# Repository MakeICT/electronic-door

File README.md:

# Master Control Program 

This system is used to secure spaces with an electronic door latch.

## Dependencies:
* [Node + NPM](Node.js)
* [PostgreSQL](http://www.postgresql.org/)
* [Arduino 1.6.5](https://www.arduino.cc/)

## Hardware requirements: 
* [Server protocol RS-485](https://en.wikipedia.org/wiki/RS-485) for the server/client communication.
* [Arduino Nano](https://www.arduino.cc/) for the door client (This is required for the matching footprint).
* [NFC reader](https://www.adafruit.com/products/364). This is the one that we are using for our version of the door lock. 

* * *

## Todo
* Server
	* Super admins vs group admins
	* Make plugins respect disabled mode
	* When unlocking from web ui, display user in log
	
* Client
	* New NFC reader
	* Add doorbell input (capacitive?)
	* Design/build case for front
	* Build 2nd client for testing & back door

## License 

> Copyright (C) 2014-2016 MakeICT
> 
> This program is free software: you can redistribute it and/or modify it 
> under the terms of the GNU General Public License as published by the 
> Free Software Foundation, either version 3 of the License, or (at your 
> option) any later version.
> 
> This program is distributed in the hope that it will be useful, but 
> WITHOUT ANY WARRANTY; without even the implied warranty of 
> MERCHANTABILITY or FITNESS FOR A PARTICULAR PURPOSE.  See the GNU 
> General Public License for more details.
> 
> You should have received a copy of the GNU General Public License along 
> with this program.  If not, see [The GNU licenses page](http://www.gnu.org/licenses)
    
* * *

This is a work in progress. For more information, please visit the [MakeICT Wiki](http://makeict.org/wiki/index.php/Electronic_Door_Entry).

* * *

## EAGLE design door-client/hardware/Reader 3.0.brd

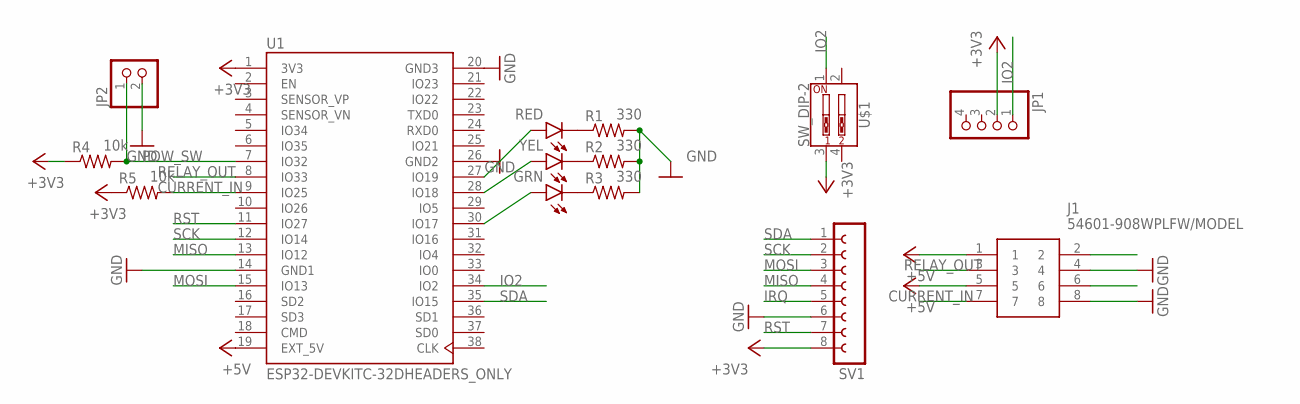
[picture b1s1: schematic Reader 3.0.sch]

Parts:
GRN: LED5MM
J1: 54601-908WPLFW/MODEL; HDRV4W64P254_1X4_1016X508X838B
JP1: PINHD-1X4/90; 1X04/90
JP2: PINHD-1X2/90; 1X02/90
R1, R2, R3: 330; 0204/7
R4, R5: 10k; 0204/7
RED: LED5MM
SV1: FE08-1; HDR_F_1X8
U1: ESP32-DEVKITC-32DHEADERS_ONLY; ESP32_DEVKITC_DIP
U$1: SW_DIP-2
YEL: LED5MM

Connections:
+3V3: JP1.2, R4.1, R5.1, SV1.8, U1.1 (3V3), U$1.3
+5V: J1.1, J1.5, U1.19 (EXT_5V)
CURRENT_IN: J1.7, R5.2, U1.9 (IO25)
GND: J1.4, J1.8, JP2.2, R1.2, R2.2, R3.2, SV1.6, U1.14 (GND1), U1.20 (GND3), U1.26 (GND2)
IO2: JP1.1, U1.34 (IO2), U$1.1
IRQ: SV1.5
MISO: SV1.4, U1.13 (IO12)
MOSI: SV1.3, U1.15 (IO13)
unnamed: GRN.A, U1.30 (IO17)
unnamed: U1.28 (IO18), YEL.A
unnamed: RED.A, U1.27 (IO19)
unnamed: R1.1, RED.K (C)
unnamed: R2.1, YEL.K (C)
unnamed: GRN.K (C), R3.1
POW_SW: JP2.1, R4.2, U1.7 (IO32)
RELAY_OUT: J1.3, U1.8 (IO33)
RST: SV1.7, U1.11 (IO27)
SCK: SV1.2, U1.12 (IO14)
SDA: SV1.1, U1.35 (IO15)

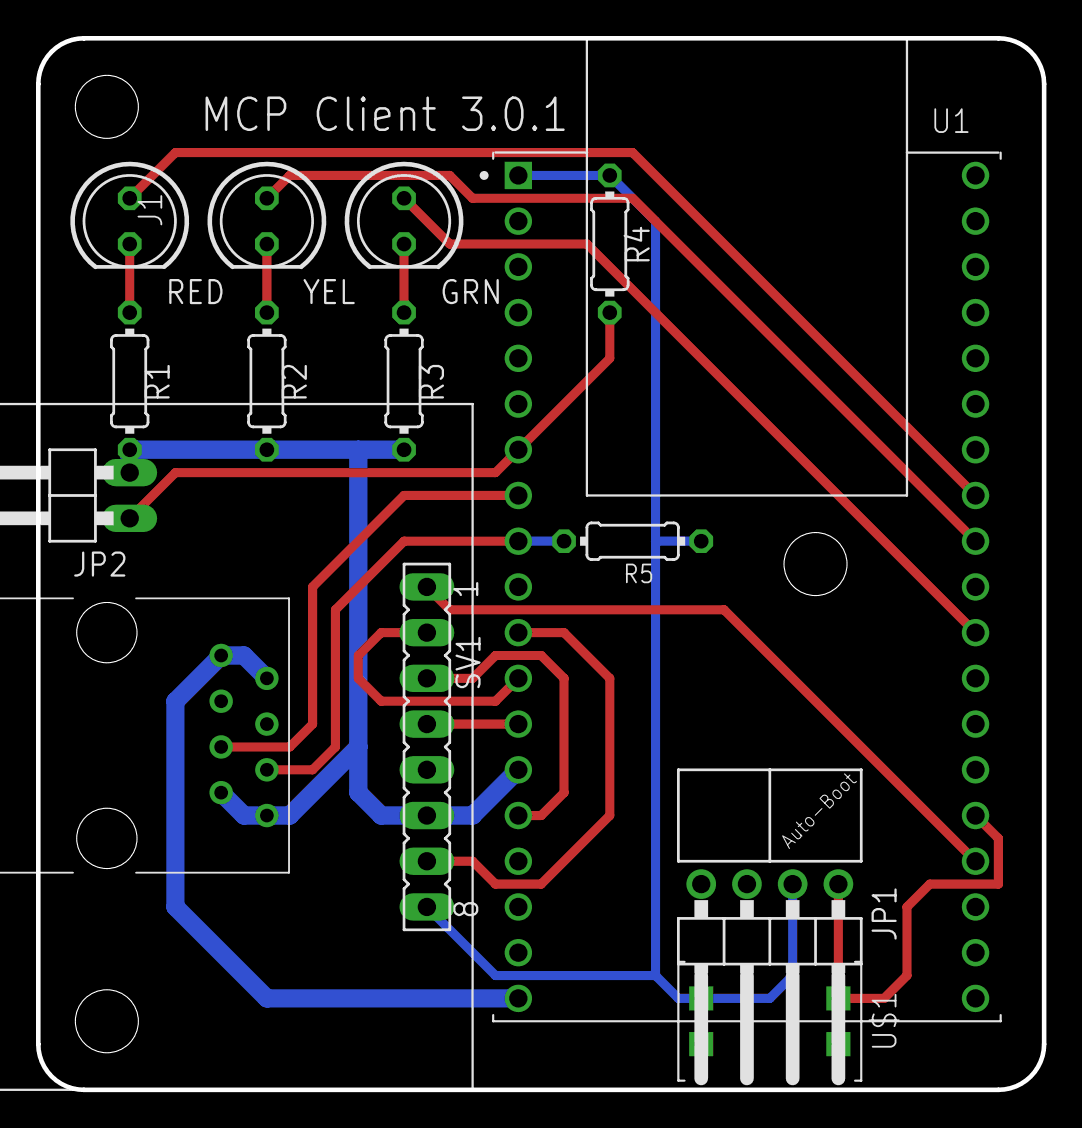
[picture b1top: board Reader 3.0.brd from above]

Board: 2 copper layers, 55.9 x 58.4 mm, 14 parts (0 on the bottom side), 18 nets.

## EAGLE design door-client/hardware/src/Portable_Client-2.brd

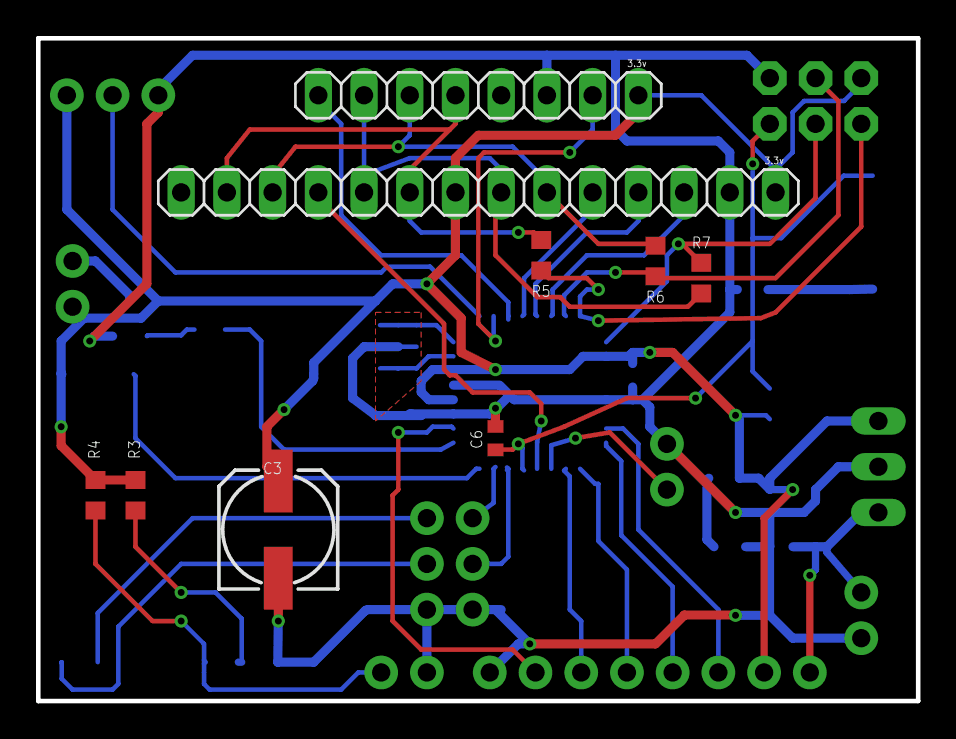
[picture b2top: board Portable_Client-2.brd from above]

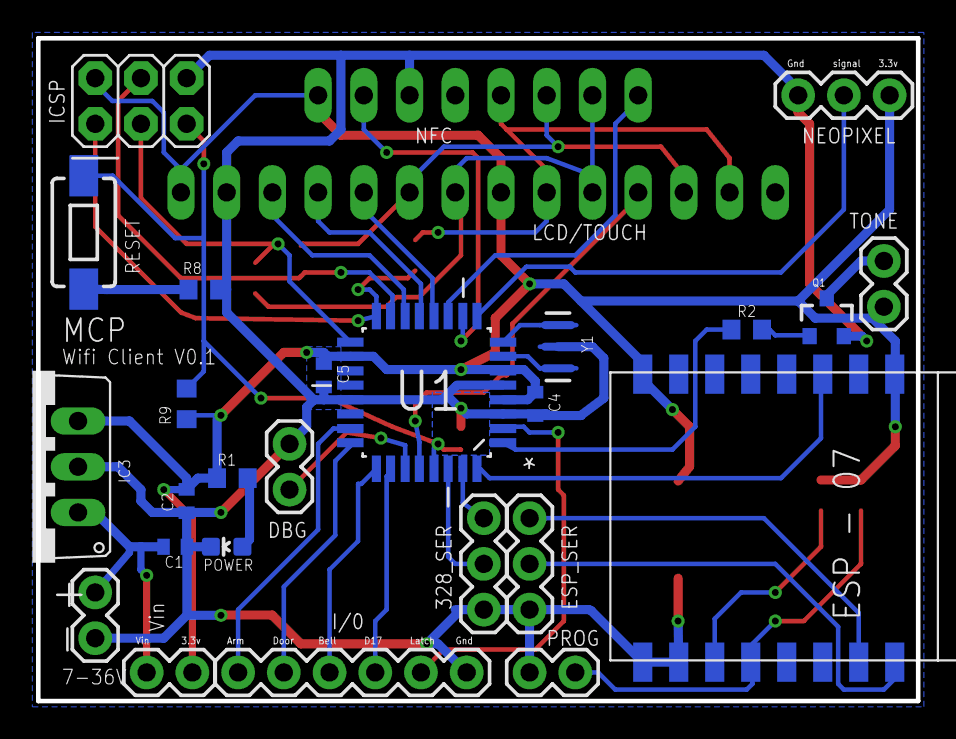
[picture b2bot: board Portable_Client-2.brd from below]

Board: 2 copper layers, 48.9 x 36.8 mm, 34 parts (25 on the bottom side), 37 nets.

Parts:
328_SER: 1X03
C1, C2: C0402
C3: 100uf; 153CLV-0605
C4, C5, C6: .1uf; C0402
DBG, DBG1: 1X02
ESP_SER: 1X03
I/0: 1X06
IC3: MC78M05ABT; TO220V
ICSP: 2X03
LCD/TOUCH: 1X14
NEOPIXEL: 1X03
NFC: 1X08
POW: 1X02
POWER: LED-0603
PROG: 1X02
Q1: SOT23-3
R1, R2, R5, R6, R7, R8: 330; R0603
R3, R4: 3.3k; R0603
R9: 4.7k; R0603
RESET: SWITCH-MOMENTARY-2SMD-1101NE; TACTILE-SWITCH-1101NE
TONE: 1X02
U1: ATMEGA328P-AU; QFP80P900X900X120-32N
U$2: ESP07-AITHINKER
Y1: 12MHZ; RESONATOR-SMD

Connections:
0SC2: U1.8, Y1.3
3V3: C2.1, C3.+, C4.1, C5.1, DBG1.2, IC3.3, ICSP.2, LCD/TOUCH.7, LCD/TOUCH.14, NEOPIXEL.1, NFC.1, R1.2, R3.1, R4.1, R9.1, TONE.1, U1.4, U1.6, U1.18, U$2.RESET1, U$2.VCC1
D0: 328_SER.2, U1.30
D1: 328_SER.3, U1.31
D2: U1.32, U$2.CH_PD1
D3: R2.2, U1.1
D4: I/0.2, U1.2
D5: NEOPIXEL.2, U1.9
D6: NFC.2, U1.10
D7: NFC.8, U1.11
D8: LCD/TOUCH.10, U1.12
D9: LCD/TOUCH.11, U1.13
D10: LCD/TOUCH.12, U1.14
D11: ICSP.4, R6.1, U1.15
D12: ICSP.1, R5.1, U1.16
D13: ICSP.3, R7.1, U1.17
D14: I/0.6, U1.23
D15: I/0.5, U1.24
D16: I/0.4, U1.25
D17: I/0.3, U1.26
D18: DBG.1, U1.27
D19: LCD/TOUCH.4, U1.28
ESP_RX: ESP_SER.3, U$2.RX1
ESP_TX: ESP_SER.2, U$2.TX1
GND: 328_SER.1, C1.2, C2.2, C3.-, C4.2, C5.2, C6.2, DBG.2, ESP_SER.1, I/0.1, IC3.2, ICSP.6, LCD/TOUCH.13, NEOPIXEL.3, NFC.3, POW.1, POWER.C, PROG.1, Q1.2, R8.1, U1.3, U1.5, U1.21, U$2.GND1, U$2.GPIO15, Y1.2
MISO: LCD/TOUCH.2, LCD/TOUCH.6, NFC.5, R5.2
MOSI: LCD/TOUCH.3, LCD/TOUCH.9, NFC.6, R6.2
unnamed: Q1.3, TONE.2
unnamed: Q1.1, R2.1
unnamed: R8.2, RESET.2
unnamed: PROG.2, R4.2, U$2.GPIO0
unnamed: R3.2, U$2.GPIO2
unnamed: POWER.A, R1.1
OSC1: U1.7, Y1.1
RESET: C6.1, ICSP.5, R9.2, RESET.1, U1.29
SCK: LCD/TOUCH.5, LCD/TOUCH.8, NFC.7, R7.2
VIN: C1.1, DBG1.1, IC3.1, POW.2

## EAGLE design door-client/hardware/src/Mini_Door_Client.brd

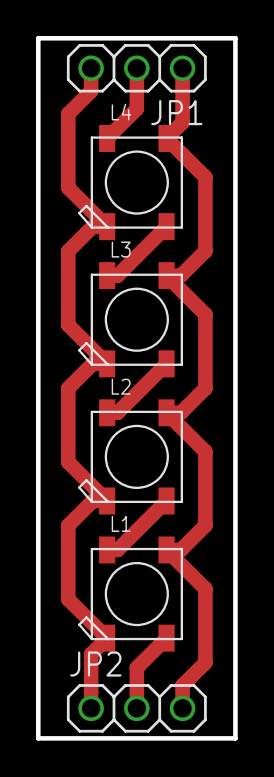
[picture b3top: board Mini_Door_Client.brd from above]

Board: 2 copper layers, 11.0 x 38.9 mm, 6 parts (0 on the bottom side), 7 nets.

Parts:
JP1, JP2: 1X03
L1, L2, L3, L4: WS2812B

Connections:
+5V: JP1.1, JP2.3, L1.1-VDD, L2.1-VDD, L3.1-VDD, L4.1-VDD
GND: JP1.3, JP2.1, L1.3-GND, L2.3-GND, L3.3-GND, L4.3-GND
unnamed: L1.2-DOUT, L2.4-DIN
unnamed: L2.2-DOUT, L3.4-DIN
unnamed: L3.2-DOUT, L4.4-DIN
unnamed: JP1.2, L4.2-DOUT
unnamed: JP2.2, L1.4-DIN

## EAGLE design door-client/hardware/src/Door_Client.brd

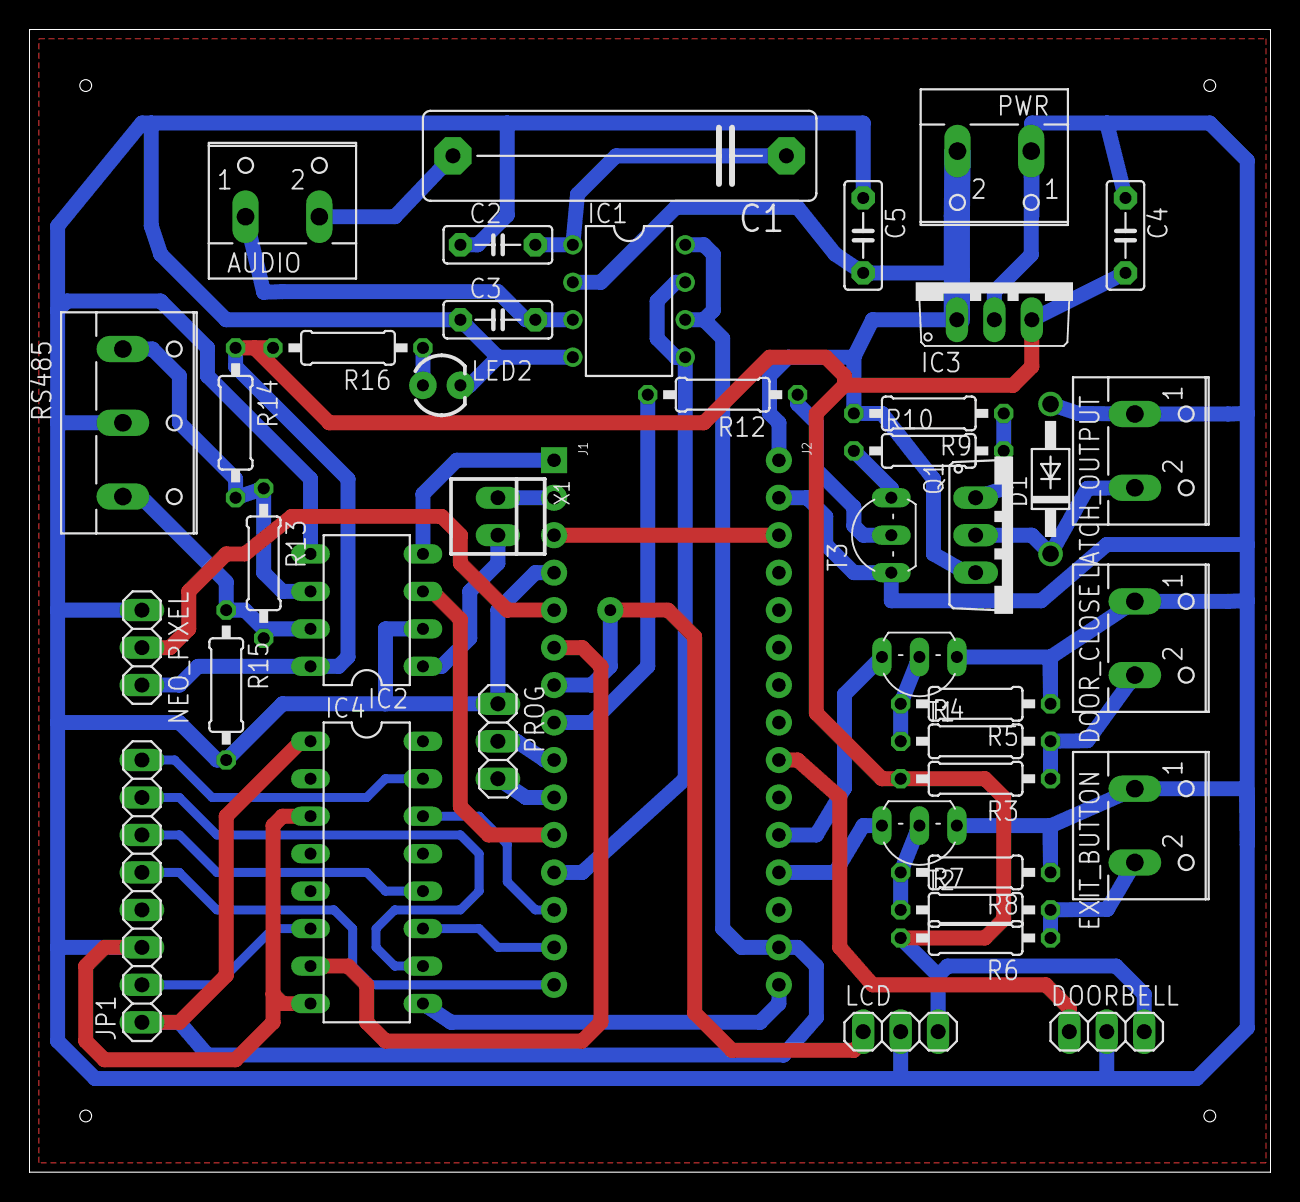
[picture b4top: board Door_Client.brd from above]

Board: 2 copper layers, 84.1 x 77.5 mm, 42 parts (0 on the bottom side), 41 nets.

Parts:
AUDIO: W237-102
C1: 10uf; C22.5B6
C2, C3, C4, C5: .1uf; C5B2.5
D1: 1N4004; DO41-10
DOORBELL: 1X03
DOOR_CLOSE: W237-102
EXIT_BUTTON: W237-102
IC1: L272M; DIL08
IC2: MAX3468EPA; DIL08
IC3: MC78M05ABT; TO220V
IC4: 4050N; DIL16
J1: HEAD15-NOSS
J2: HEAD15-NOSS-1
JP1: 1X08
LATCH_OUTPUT: W237-102
LCD: 1X03
LED2: LED3MM
NEO_PIXEL: 1X03
PROG: 1X03
PWR: W237-102
Q1: TIP42C; TO220AV
R3, R4, R5, R6, R7, R8, R9: 10K; 0207/10
R10: 2k; 0207/10
R12: 0207/10
R13: 100; 0207/10
R14, R15: 20K; 0207/10
R16: 330; 0207/10
RS485: W237-103
T1, T2, T3: TO92-EBC
X1: 22-23-2021

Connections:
3V3: IC1.6, IC1.8, IC4.1, J2.14, JP1.1
+5V: C4.2, DOORBELL.3, IC2.8, IC3.3, LCD.3, NEO_PIXEL.3, R3.2, R6.2, R14.1, R16.2
A0: J2.12, T2.C
A1: J2.11, T1.C
A3: DOORBELL.1, J2.9
COM: C2.1, C3.1, C4.1, C5.1, D1.A, DOORBELL.2, DOOR_CLOSE.1, EXIT_BUTTON.1, IC1.4, IC2.2, IC2.5, IC3.2, IC4.3, IC4.8, J1.4, J2.2, JP1.3, LATCH_OUTPUT.1, LCD.2, LED2.K, NEO_PIXEL.1, PROG.1, PWR.1, R5.1, R8.1, R15.2, RS485.2, T1.E, T2.E, T3.E
D2: J1.5, NEO_PIXEL.2
D3: IC4.7, J1.6
D4: J1.7, LCD.1
D6: J1.2, X1.1
D7: IC2.4, J1.1
D8: IC2.3, J1.11
D9: IC1.5, IC1.7, J1.12
D10: IC4.14, J1.13
D11/MOSI: IC4.11, J1.14
D12/MISO: J1.15, JP1.5
D13: J1.8, R12.2
unnamed: D1.C, LATCH_OUTPUT.2, Q1.C
unnamed: R12.1, T3.B
unnamed: IC4.6, JP1.2
unnamed: IC2.7, R13.2, R15.1, RS485.3
unnamed: IC2.6, R13.1, R14.2, RS485.1
unnamed: J1.9, PROG.2
unnamed: C1.1, C2.2, IC1.1
unnamed: AUDIO.2, C1.2
unnamed: AUDIO.1, C3.2, IC1.3
unnamed: LED2.A, R16.1
unnamed: R4.1, R5.2, T1.B
unnamed: DOOR_CLOSE.2, R3.1, R4.2
unnamed: R7.1, R8.2, T2.B
unnamed: EXIT_BUTTON.2, R6.1, R7.2
unnamed: R10.1, T3.C
unnamed: Q1.B, R9.1, R10.2
unnamed: IC4.10, JP1.7
unnamed: IC4.12, JP1.6
unnamed: IC4.15, JP1.8
unnamed: J1.10, PROG.3
unnamed: IC4.9, J2.15
unnamed: IC2.1, X1.2
RESET: J1.3, J2.3
VIN: C5.2, IC1.2, IC3.1, J2.1, PWR.2, Q1.E, R9.2

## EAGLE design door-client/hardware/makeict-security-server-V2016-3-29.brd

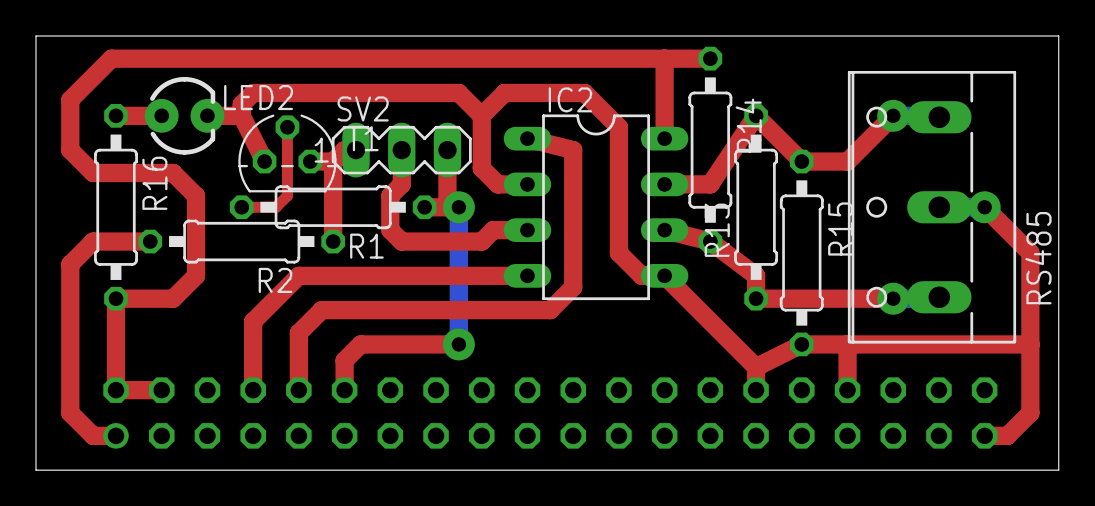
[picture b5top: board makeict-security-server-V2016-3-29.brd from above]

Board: 2 copper layers, 56.8 x 24.1 mm, 12 parts (1 on the bottom side), 12 nets.

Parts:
IC2: MAX3468EPA; DIL08
LED2: LED3MM
R1, R2: 4.7K; 0207/10
R13: 100; 0207/10
R14, R15: 20K; 0207/10
R16: 330; 0207/10
RS485: W237-103
SV1: FE20-2
SV2: MA03-1
T1: 2N3904; TO92

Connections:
+3V3: R2.2, SV1.1, SV1.17
+5V: IC2.8, R14.1, R16.2, SV1.2, SV1.4
COM: IC2.2, IC2.5, LED2.K, R15.2, RS485.2, SV1.6, SV1.9, SV1.14, SV1.20, SV1.25, SV1.30, SV1.34, SV1.39, T1.3
D7: IC2.4, SV1.8
D8: IC2.3, SV2.2
unnamed: R1.1, SV1.12, SV2.3
unnamed: R1.2, T1.2
unnamed: R2.1, SV2.1, T1.1
unnamed: IC2.7, R13.2, R15.1, RS485.3
unnamed: IC2.6, R13.1, R14.2, RS485.1
unnamed: LED2.A, R16.1
unnamed: IC2.1, SV1.10

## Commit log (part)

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2016-04-04 show login if authentication is stale
2016-04-04 rename to system tools; add system tools
2016-04-04 fix bug from bad copy-paste
2016-04-06 force door unlock duration to 2 bytes
2016-04-06 fix for 2 byte duration
2016-04-06 add more logging
2016-04-06 wrong code
2016-04-06 drop masonry
2016-04-06 fix plugin action button appearance
2016-04-06 fix error on unauth
2016-04-06 forgot serial patches
2016-04-06 don't strip spaces
2016-04-06 center plugin enable/disable buttons
2016-04-06 fix wildapricot group bug; better logging
2016-04-06 front-end UX improvements
2016-04-06 fix bug with enable/disable plugin
2016-04-06 fix bug when enable/disable plugins
2016-04-13 add delay before issuing system commands
2016-04-19 change user display to wells
2016-04-19 autoload user groups
2016-04-20 add basic chime stuff
2016-04-20 allow users to add groups
2016-04-20 add tone for alarm
2016-04-27 change plugin option format
2016-04-27 holy crap, you can BIND functions to a THIS arg before calling them?! Sweet jesus.
2016-04-27 fix packet queing system maybe...
2016-04-27 eliminate race condition with plugin settings load. Asynch is not my friend :(
2016-04-28 fix plugin loading bug on first run
2016-05-01 fix serial boo-boos - don't wait for response on ACKs and resend the last non-ACK packet. Oops. - properly increment transaction ID when sending new packets
2016-05-04 only send to clients who have this plugin installed
2016-05-04 fix installation bug with client plugins
2016-05-04 add ability to update clients
2016-05-04 super serial needs to know when a client plugin id is updated
2016-05-04 don't ascii encode...
2016-05-04 make log loads faster
2016-05-04 improve client plugin ui
2016-05-04 Add door bell, make address assignable
2016-05-11 better groups UI
2016-05-12 Fix serial issues, add conditionals for different modules -fix transaction ID not incrementing properly on received packets -improve collision detection and avoidance
2016-05-18 fix option loading
2016-05-18 no need to wait before queuing chime message
2016-05-18 accidentally deleted a line of code :-/
2016-05-25 starting scheduler stuff...
2016-06-01 don't die on no credentials
2016-06-01 create params for actions
2016-06-02 mostly GUI stuff for event scheduler
2016-06-17 action parameters saving and loading
2016-06-17 saving jobs and parameters works
2016-06-17 fix paramters for jobs enabled by startup
2016-06-18 fix serial data from Chime plugin
2016-06-18 changes to accommodate user modifications
2016-06-19 save user name and email
2016-06-20 fix log controller
2016-06-20 remove birthday check when remote unlocking
2016-06-22 improve interface for managing users
2016-06-22 fix user join date syncing
2016-06-22 force scope apply to update UI
2016-06-28 fix backups
2016-06-28 UI fixes and improvements
2016-07-04 catch error with serial resends
2016-07-04 always send HTTP cookies
2016-07-04 update api url
2016-07-04 collapse navbar on mobile
2016-07-06 make logo smaller
2016-07-07 Fix same ID resend timeout
2016-07-13 slight code cleanup
2016-07-13 switch to broadcasts; fix LCD idle timer
2016-07-13 add broadcast and some debug output
2016-07-14 Fix client handling of broadcast packets
2016-07-15 Tune previews
2016-07-15 show user's key
2016-07-16 Add makefile for driver source, restructure source and libs
2016-07-16 Add serial message on client start
2016-07-17 auto expand single user search result
2016-07-17 fix WildApricot sync errors
2016-07-17 slow down sync a bit
2016-07-17 missed square brackets - not sure if this caused any problems
2016-07-17 Move module configuration to makefile
2016-07-18 Add first run detection
2016-07-18 Add setting address to default on first run
2016-07-19 Fix handling of client address initialization
2016-07-19 add more debugging
2016-07-19 Fix char* warning in lcd library
2016-07-21 add more logging for alarm status
2016-07-21 Minor formatting changes
2016-07-22 hide some noisy serial debug lines
2016-07-23 Eagle PC board files and mill files
    Current board files as of July 2016 Tom
2016-07-23 type param no longer needed
2016-07-26 Add serial watchdog
2016-07-26 clean up debug
2016-07-27 Add watchdog timer to prevent client freezes
2016-07-27 slow down reconnects
2016-07-27 give super serial time to load before sending stuff
2016-07-27 stop dying you piece of crash
2016-07-28 auto-reconnect alarm decoder on failure
2016-07-28 conform reconnect actions on watchdog timer
2016-07-29 Add hard reset for NFC reader after 2 failed attempts to restart it -also initialize some variable and clean some formatting
2016-07-29 Add forced reset if reader cannot be recovered
2016-07-29 make it play noise when the alarm is armed
2016-08-01 Modify reader failure detection and recovery
2016-08-01 Modify config command processing
2016-08-01 Improve reader failure reset logic
2016-08-02 add delay to make sure the new status is real
2016-08-02 Read doorState at beginning to prevent false updates
2016-08-03 expand configuration saving/loading, add structs for tunes and lights
2016-08-03 fix bug where disabled serial plugin keeps trying to reconnect
2016-08-03 Finish config improvements, add handling for configuration over serial
2016-08-03 Clean up some config errors, use EEPROM config for lights and sounds
2016-08-03 Fix config save/load error, add configs for wait and error lights
2016-08-04 re-add mistakenly removed light sequence when unlocking
2016-08-04 Fix config save/load to get all of the proper values -load same address as save (duh) -fix saving of start tune -modify audio to work with new config
2016-08-04 Remove unnecessary struct and function from config class
2016-08-07 Re-arrange reader code
2016-08-24 tweak NFC read error detection
2016-08-30 make restore script executable
2016-08-30 fix bug where key field collapses on new enrollment
2016-08-30 Fix action loading bug on job scheduler page
2016-08-30 Add missing require to doorbell
2016-08-30 Log data when doorbell pressed
2016-08-30 Use correct message parameter
2016-08-31 Make it easier to re-assign past keys
2016-08-31 hide NFC history after assignment
2016-08-31 Semi-working doorbell plugin
2016-09-06 Brian is whining about the grainy audio.
2016-09-27 just a little code cleanup
2016-10-02 disable pings
2016-10-03 allow deletion of plugins
2016-11-29 log a useful error message
2016-12-07 change pin assignments
2017-01-01 make latch work when no door switch is present
2017-01-11 minor code clean-up -resolve warnings -re-configure some pre-processor directives in reader.cpp
2017-01-11 fix some whitespace, minor re-formatting
2017-01-15 fix bug when no search terms are present
2017-01-15 Minor logging additions.
2017-01-16 update .gitignore, add new board files, put gcode files in new folder
2017-01-17 enable autoscroll in console
2017-01-17 don't show auto-login error; make login focus on load
2017-01-17 add client name to arm messaging
2017-01-19 New client board V0.1
2017-01-19 add lib files
2017-01-31 Move pin definitions to definitions.h, fix doorbell input declaration
2017-02-01 Redefine pnis for new board layout
2017-02-01 fix a few board errors -MOSI and MISO swapped on LCD and SPI headers -change esp8266 capacitor to surface mount
2017-02-07 Fix DRC errors in wifi client board.
2017-02-08 re-assign pins for original board layout
2017-02-08 fix logging type bug
2017-02-08 fix pin name
2017-02-08 remove ili9340 code
2017-02-09 add module class
2017-02-09 rearrange lib files, make ring a subclass of module
2017-02-10 convert reader to subclass of module
2017-02-10 move definitions and utils to library folder
2017-02-10 add wifi and glcd modules
2017-02-10 re-route swapped pins on board
2017-02-10 re-route sections to shorten traces and reduce number of vias
2017-03-17 make logs link to user
2017-06-21 Suspended members are now treated as inactive.
2017-06-25 add basic log filtering -add filtering to backend api -add buttons in frontend -this code is probably awful
2017-07-16 move files
2017-07-16 ignore virtualenv
2017-07-16 fix frontend
2017-07-20 convert setup for python deps
2017-07-21 clear out old stuff
2017-08-01 setting/retrieving plugin options
2017-09-01 hard version numbers
2017-09-07 fix imports
2017-12-15 make user search works
2017-12-25 stub out API function calls
2017-12-26 add basic authorization
2017-12-27 add search tags for groups and auth tags
2017-12-27 add client handling code
2017-12-29 Support for client/plugin associations and c/p settings
2017-12-29 add support for plugin actions
2017-12-29 add support for client-plugin actions
2018-01-04 sync WA user groups
2018-01-06 add python code for interfacing with MCP API
2018-01-07 fix print statements in rpi.py
2018-01-09 fix rc522 library
2018-01-13 rudimentary wifi card authenticator
2018-01-14 tweak status lights
2018-01-14 add button to turn off machine
2018-01-15 clean up GPIO on exit
2018-01-16 testing pyqt5
2018-01-16 drop pyside (qt4) for pyqt5
2018-01-16 fix log format check
2018-03-19 modify local backup, fix non-members being marked as active
2018-03-24 adjust code for power switch instead of off button
2018-03-24 add setup script to install service
2018-03-26 updating gitignore file to ignore my files
2018-04-01 add more detailed logging, slightly restructure
2018-04-08 add debug output for api requests failure
2018-04-09 Add support to UpSync™ user groups to WildApricot
2018-04-12 Revert code that prevented email from updating - can't replicate bug
2018-07-07 change annoying messages to debug level
2018-08-10 Add files for esp32 client
2018-08-16 Add base code for mfrc522 reader, refactor for cpp compatibility
2018-08-16 add api calls to get user info by nfcID and write logs
2018-08-17 Revert "Merge remote-tracking branch 'origin/wa-group-sync'"
    This reverts commit 54b5d8e150ad7e0e4865f198cab9eac910a1ec0e, reversing
    changes made to 074487d746b38bfc18ec2273d6efaf38c6b4b505.
2018-08-17 add missing dependencies
2018-08-17 add mor missing dependencies
2018-08-17 fix logging function
2018-08-19 add sdkconfig.default, remove sdkconfig from tracking, update .gitignore
2018-08-20 fix bug in fetching HTTP responses
2018-08-23 fix logging issues, change nfcID to lowercase hex
2019-01-11 modify WA sync so that users who make partial payments are not immediately deactivated
2019-02-19 update gitignore
2019-03-02 fix nfc key assignment filter
2019-03-02 fix log filtering
2019-03-02 make filter strings ignore case
2019-03-02 add simple paging to log page
2019-03-03 only show giant logo header when not logged in
2019-03-03 force page number input to be treated as int
2019-03-03 add ui for filtering by message
2019-03-03 fix bug in log filter creation loop
2019-03-05 remove old board files
2019-03-05 add rj45 jack to board
2019-03-05 use new api endpoint to check group enrollment
2019-03-05 change unlock pin
2019-03-05 re-order the power off sequence so green light doesn't stay on if network is slow
2019-03-12 Slight adjustments to board layout, add pullup resistor
2019-04-09 Fix LED pin assignments, update SPI.cpp for new SDK version
2019-06-28 Change WA Sync to reduce log spam
2019-07-26 add baseline for new flask server
2019-07-26 fix initial database migration downgrade file
2019-07-26 add first and last name fields to user update form make form easier to add fields
2019-07-26 Fix display of text field input errors
2019-07-26 Fix page title
2019-07-26 add profile pic directory to .gitignore
2019-07-26 set flask to run in development mode
2019-07-26 swap flask_login for flask_user
2019-08-07 fix formatting to conform with PEP-8
2020-04-29 Bump jquery from 2.2.4 to 3.5.0 in /server/software
    Bumps [jquery](https://github.com/jquery/jquery) from 2.2.4 to 3.5.0.
    - [Release notes](https://github.com/jquery/jquery/releases)
    - [Commits](https://github.com/jquery/jquery/compare/2.2.4...3.5.0)
2020-08-20 Bump bcrypt from 0.8.5 to 5.0.0 in /server/software
    Bumps [bcrypt](https://github.com/kelektiv/node.bcrypt.js) from 0.8.5 to 5.0.0.
    - [Release notes](https://github.com/kelektiv/node.bcrypt.js/releases)
    - [Changelog](https://github.com/kelektiv/node.bcrypt.js/blob/master/CHANGELOG.md)
    - [Commits](https://github.com/kelektiv/node.bcrypt.js/compare/v0.8.5...v5.0.0)

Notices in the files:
parts and their libraries:
SparkFun-LED: Licensing: CC v3.0 Share-Alike You are welcome to use this library for commercial purposes.
SparkFun-Connectors: Licensing: Creative Commons ShareAlike 4.0 International - https://creativecommons.org/licenses/by-sa/4.0
